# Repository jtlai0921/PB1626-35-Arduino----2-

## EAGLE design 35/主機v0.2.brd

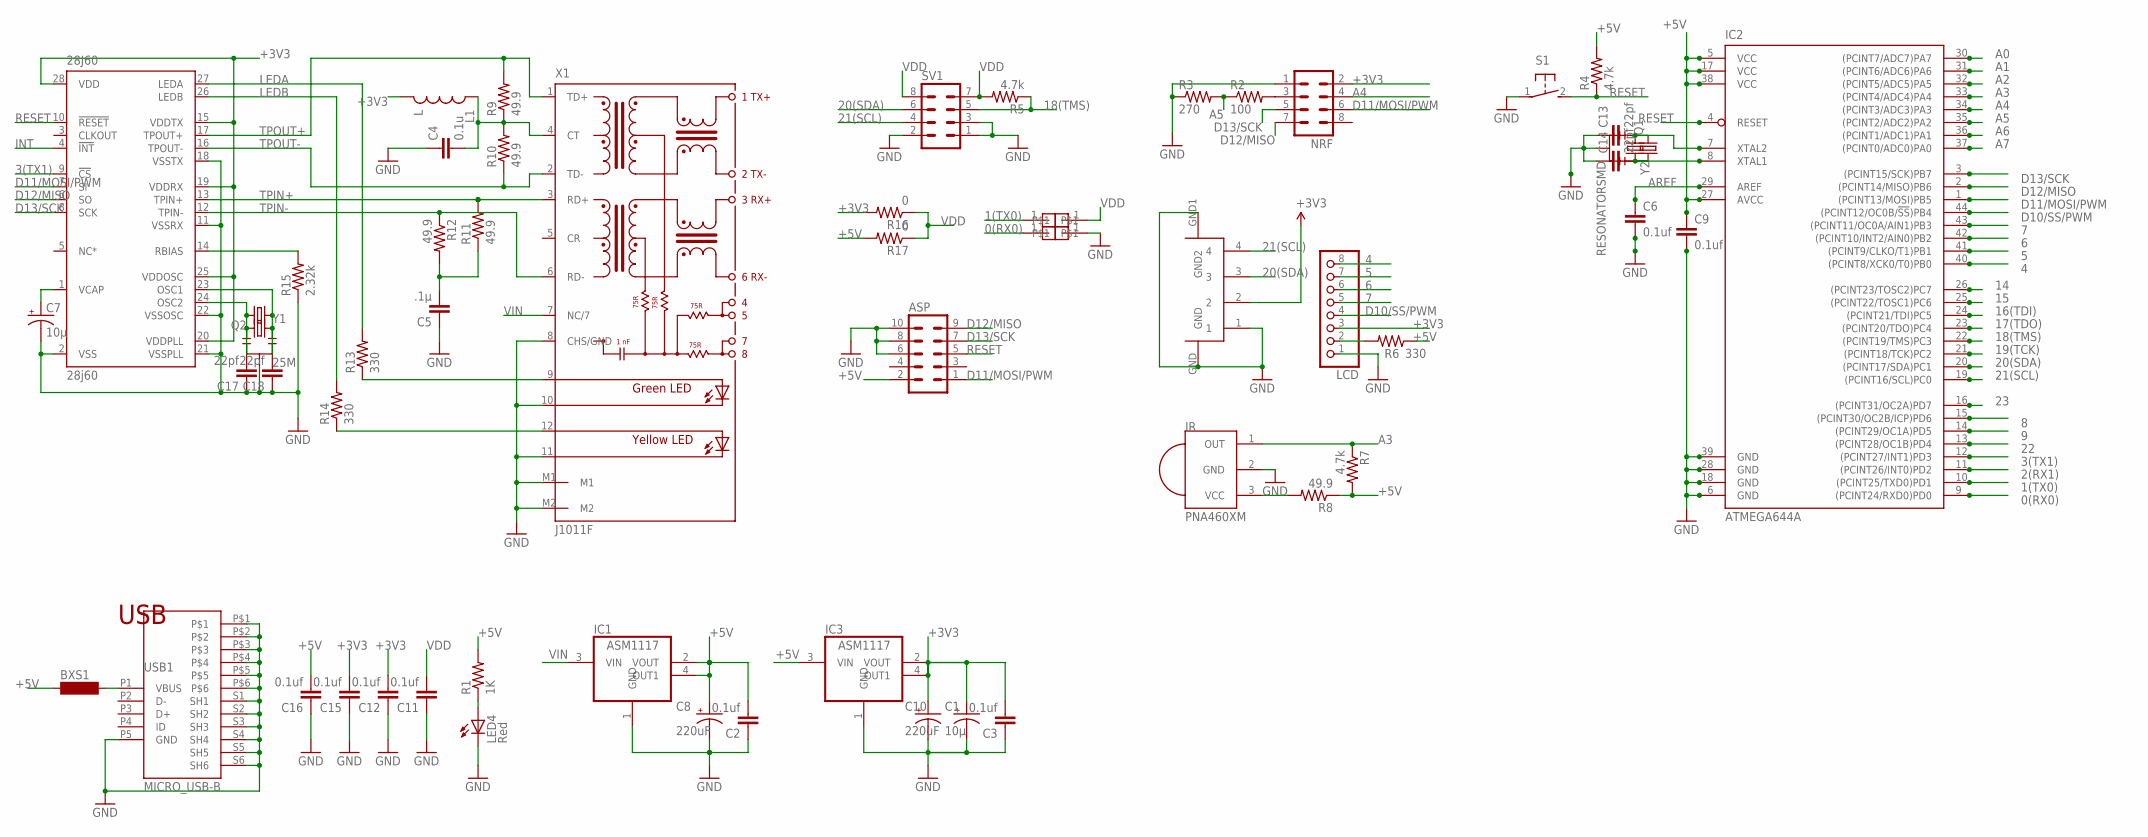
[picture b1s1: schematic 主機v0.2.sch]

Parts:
28J60: 28j60; SSOP28DB
ASP: MA05-2
BXS1: SM-1206
C1, C7: 10μ; EIA3528
C2, C3, C6, C9, C11, C12, C15, C16: 0.1uf; 0603-CAP
C4: 0.1u; 0603-CAP
C5: .1μ; 0603-CAP
C8, C10: 220uF; 153CLV-0605
C13, C14, C17, C18: 22pf; 0603-CAP
IC1: ASM1117; SOT223
IC2: ATMEGA644A; TQFP44
IC3: ASM1117; SOT223; MPN REG1117
IR: PNA460XM
L1: L; 0603
LCD: PINHD-1X8; 1X08
LED4: Red; 0805-LED
NRF: MA04-2
Q1, Q2: CRYSTALHC49S; HC49/S
R1: 1K; 0603-RES
R2: 100; 0603-RES
R3: 270; 0603-RES
R4, R5, R7: 4.7k; 0603-RES
R6, R13, R14: 330; 0603-RES
R8, R9, R10, R11, R12: 49.9; 0603-RES
R15: 2.32k; 0603-RES
R16, R17: 0; 0603-RES
S1: 31-XX; B3F-31XX
SV1: MA04-2
U$2: S4B-XH-SM4-TB; XH-SM4-TB
U$4, U$5, U$6, U$7: PIN1
USB1: MICRO_USB-B; USB_MICRO_B
X1: J1011F; HRJ
Y1: 25M; RESONATOR-SMD
Y2: RESONATORSMD; RESONATOR-SMD

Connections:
0(RX0): IC2.9 ((PCINT24/RXD0)PD0), U$7.1
1(TX0): IC2.10 ((PCINT25/TXD0)PD1), U$6.1
2(RX1): IC2.11 ((PCINT26/INT0)PD2)
3(TX1): 28J60.9 (!CS), IC2.12 ((PCINT27/INT1)PD3)
4: IC2.40 ((PCINT8/XCK0/T0)PB0), LCD.8
5: IC2.41 ((PCINT9/CLKO/T1)PB1), LCD.7
6: IC2.42 ((PCINT10/INT2/AIN0)PB2), LCD.6
7: IC2.43 ((PCINT11/OC0A/AIN1)PB3), LCD.5
8: IC2.15 ((PCINT30/OC2B/ICP)PD6)
9: IC2.14 ((PCINT29/OC1A)PD5)
14: IC2.26 ((PCINT23/TOSC2)PC7)
15: IC2.25 ((PCINT22/TOSC1)PC6)
16(TDI): IC2.24 ((PCINT21/TDI)PC5)
17(TDO): IC2.23 ((PCINT20/TDO)PC4)
18(TMS): IC2.22 ((PCINT19/TMS)PC3), R5.1, SV1.5
19(TCK): IC2.21 ((PCINT18/TCK)PC2)
20(SDA): IC2.20 ((PCINT17/SDA)PC1), SV1.6, U$2.3
21(SCL): IC2.19 ((PCINT16/SCL)PC0), SV1.4, U$2.4
22: IC2.13 ((PCINT28/OC1B)PD4)
23: IC2.16 ((PCINT31/OC2A)PD7)
+3V3: 28J60.15 (VDDTX), 28J60.19 (VDDRX), 28J60.20 (VDDPLL), 28J60.25 (VDDOSC), 28J60.28 (VDD), C1.A (+), C3.2, C10.+, C12.2, C15.2, IC3.2 (VOUT), IC3.4 (OUT1), L1.2, LCD.3, NRF.2, R16.2, U$2.2
+5V: ASP.2, BXS1.1, C2.2, C8.+, C9.1, C16.2, IC1.2 (VOUT), IC1.4 (OUT1), IC2.5 (VCC), IC2.17 (VCC), IC2.27 (AVCC), IC2.38 (VCC), IC3.3 (VIN), R1.2, R4.2, R6.1, R7.2, R8.1, R17.2
A0: IC2.30 ((PCINT7/ADC7)PA7)
A1: IC2.31 ((PCINT6/ADC6)PA6)
A2: IC2.32 ((PCINT5/ADC5)PA5)
A3: IC2.33 ((PCINT4/ADC4)PA4), IR.1 (OUT), R7.1
A4: IC2.34 ((PCINT3/ADC3)PA3), NRF.4
A5: IC2.35 ((PCINT2/ADC2)PA2), R2.1, R3.2
A6: IC2.36 ((PCINT1/ADC1)PA1)
A7: IC2.37 ((PCINT0/ADC0)PA0)
AREF: C6.1, IC2.29 (AREF)
D10/SS/PWM: IC2.44 ((PCINT12/OC0B/!SS!)PB4), LCD.4
D11/MOSI/PWM: 28J60.7 (SI), ASP.1, IC2.1 ((PCINT13/MOSI)PB5), NRF.6
D12/MISO: 28J60.6 (SO), ASP.9, IC2.2 ((PCINT14/MISO)PB6), NRF.7
D13/SCK: 28J60.8 (SCK), ASP.7, IC2.3 ((PCINT15/SCK)PB7), NRF.5
GND: 28J60.2 (VSS), 28J60.11 (VSSRX), 28J60.18 (VSSTX), 28J60.21 (VSSPLL), 28J60.22 (VSSOSC), ASP.6, ASP.8, ASP.10, C1.C (-), C2.1, C3.1, C4.1, C5.1, C6.2, C7.C (-), C8.-, C9.2, C10.-, C11.1, C12.1, C13.1, C14.1, C15.1, C16.1, C17.1, C18.1, IC1.1 (GND), IC2.6 (GND), IC2.18 (GND), IC2.28 (GND), IC2.39 (GND), IC3.1 (GND), IR.2 (GND), LCD.1, LED4.C, NRF.1, R3.1, R15.1, S1.1, SV1.1, SV1.2, SV1.3, U$2.1, U$2.GND, U$2.GND1 (GND2), U$4.1, USB1.P5 (GND), USB1.P$1, USB1.P$2, USB1.P$3, USB1.P$4, USB1.P$5, USB1.P$6, USB1.S1 (SH1), USB1.S2 (SH2), USB1.S3 (SH3), USB1.S4 (SH4), USB1.S5 (SH5), USB1.S6 (SH6), X1.8 (CHS/GND), X1.10 (C-R), X1.11 (C-L), X1.M1, X1.M2, Y1.2, Y2.2
INT: 28J60.4 (!INT)
LEDA: 28J60.27 (LEDA), R13.2
LEDB: 28J60.26 (LEDB), R14.2
unnamed: C13.2, IC2.7 (XTAL2), Q1.2, Y2.1
unnamed: IR.3 (VCC), R8.2
unnamed: LED4.A, R1.1
unnamed: NRF.3, R2.2
unnamed: C5.2, R11.1, R12.2
unnamed: 28J60.1 (VCAP), C7.A (+)
unnamed: 28J60.14 (RBIAS), R15.2
unnamed: C14.2, IC2.8 (XTAL1), Q1.1, Y2.3
unnamed: C4.2, L1.1, R9.1, R10.2, X1.4 (CT)
unnamed: 28J60.24 (OSC2), C17.2, Q2.2, Y1.1
unnamed: 28J60.23 (OSC1), C18.2, Q2.1, Y1.3
unnamed: R13.1, X1.9 (A-R)
unnamed: R14.1, X1.12 (AL)
unnamed: LCD.2, R6.2
RESET: 28J60.10 (!RESET), ASP.5, IC2.4 (RESET), R4.1, S1.2 (S)
TPIN+: 28J60.13 (TPIN+), R11.2, X1.3 (RD+)
TPIN-: 28J60.12 (TPIN-), R12.1, X1.6 (RD-)
TPOUT+: 28J60.17 (TPOUT+), R9.2, X1.1 (TD+)
TPOUT-: 28J60.16 (TPOUT-), R10.1, X1.2 (TD-)
VDD: C11.2, R5.2, R16.1, R17.1, SV1.7, SV1.8, U$5.1
VIN: IC1.3 (VIN), X1.7 (NC/7)
VUSB: BXS1.2, USB1.P1 (VBUS)

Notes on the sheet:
USB

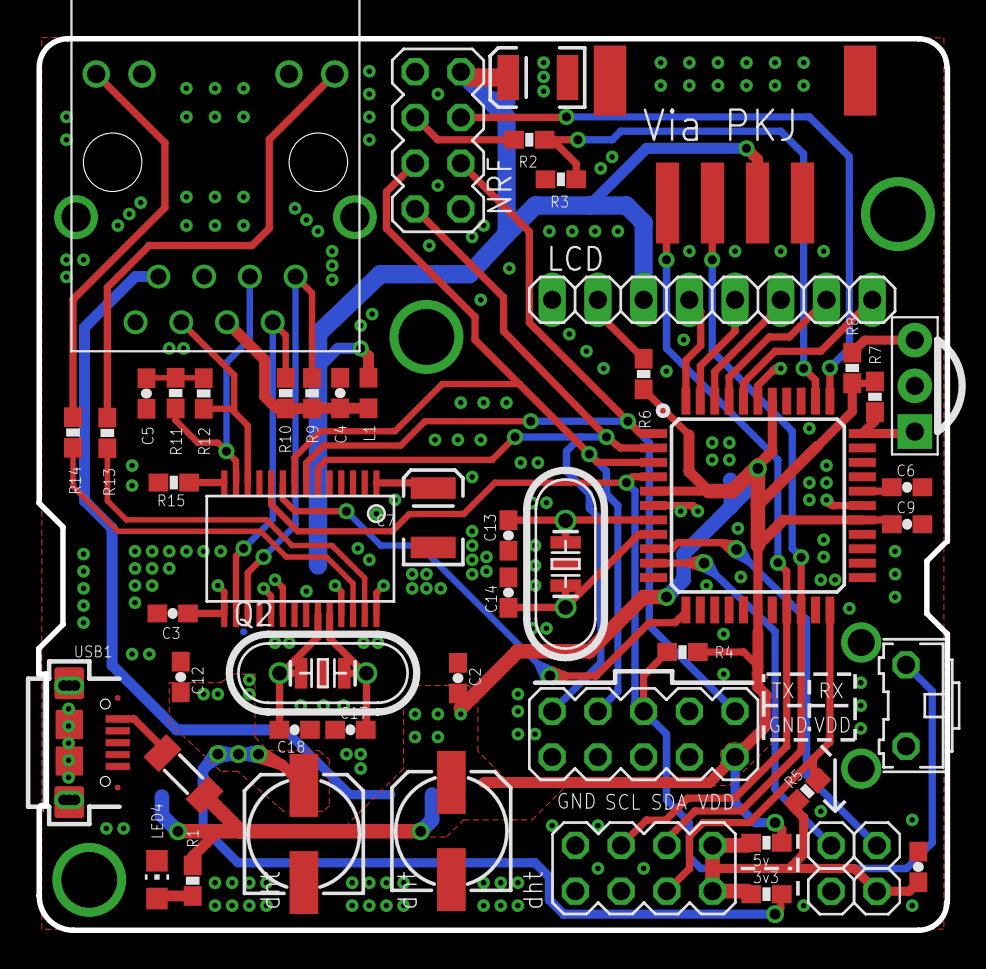
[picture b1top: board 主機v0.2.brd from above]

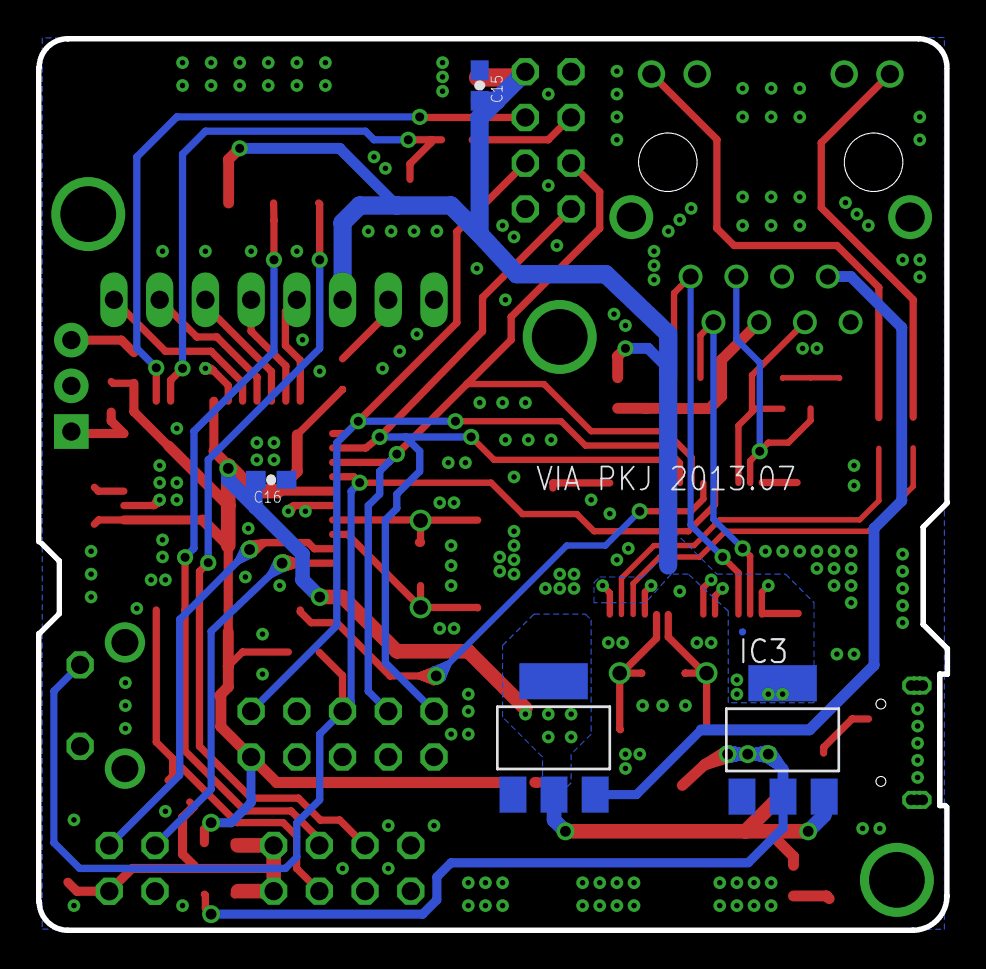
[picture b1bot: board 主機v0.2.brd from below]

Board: 2 copper layers, 50.5 x 49.5 mm, 59 parts (4 on the bottom side), 45 nets.

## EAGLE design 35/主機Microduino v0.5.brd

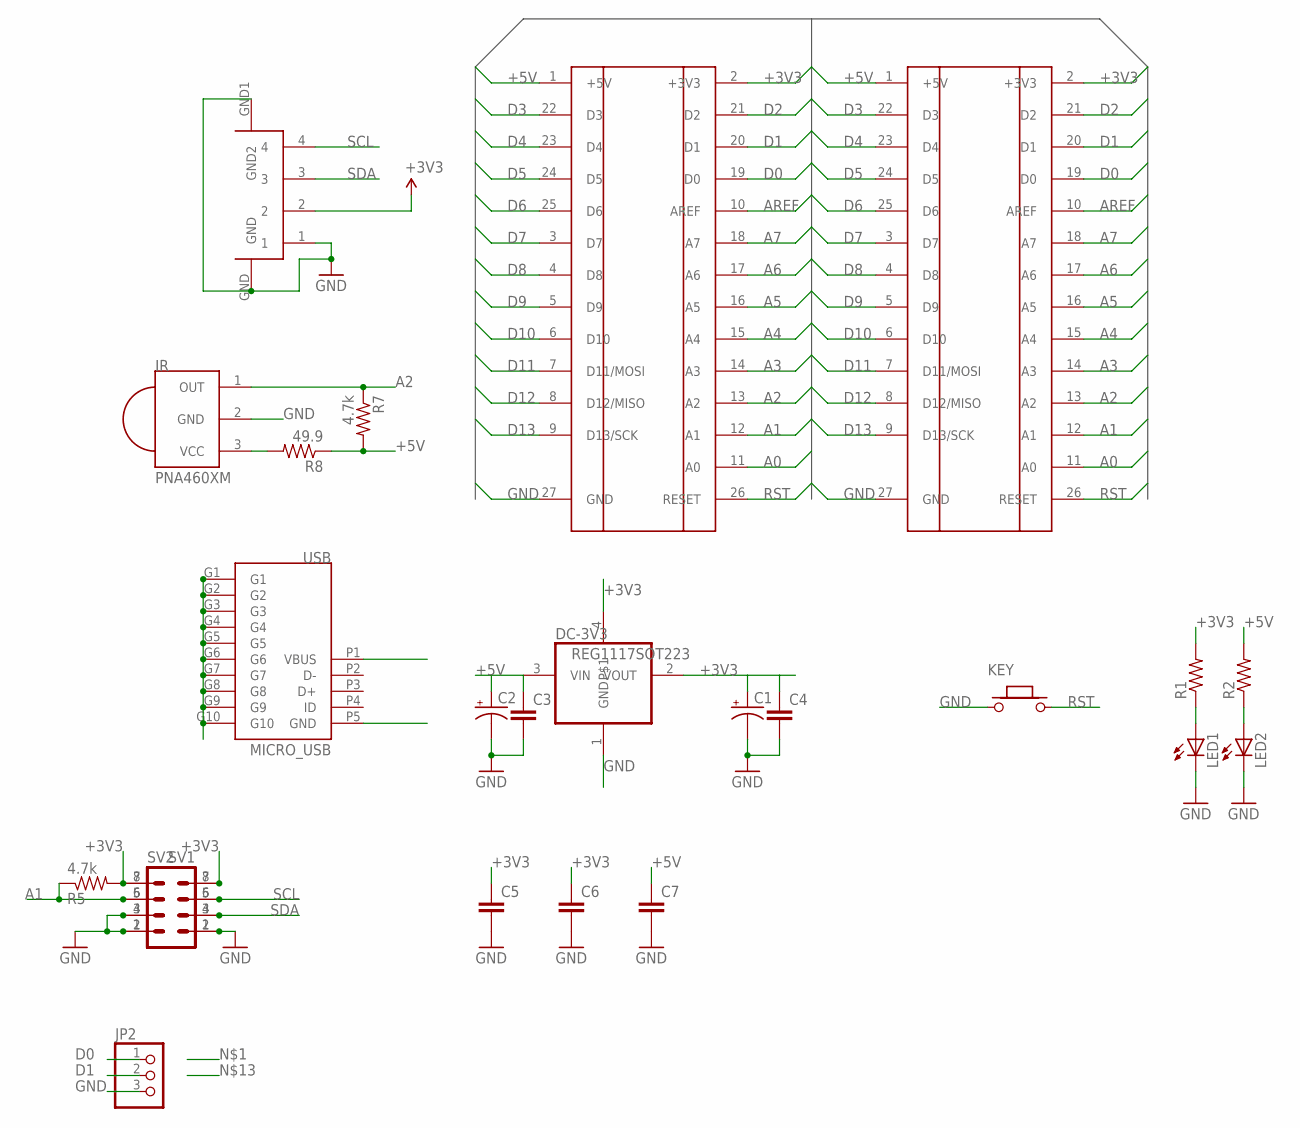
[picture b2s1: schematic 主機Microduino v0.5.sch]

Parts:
C1, C2: CAP_POL3528; EIA3528
C3, C4, C5, C6, C7: CAP0603-CAP; 0603-CAP
DC-3V3: REG1117SOT223; SOT223
IR: PNA460XM
JP2: PINHD-1X3; 1X03
KEY: KEY-TES-018; KEY-TS-018
LED1, LED2: LED0805; 0805-LED
R1, R2: RESISTOR0603-RES; 0603-RES
R5, R7: 4.7k; 0603-RES
R8: 49.9; 0603-RES
SV1, SV2: MA04-2
U$1, U$2: PING-MICRDUINO/1009; PIN-MICRODUINO-1009
U$3: S4B-XH-SM4-TB; XH-SM4-TB
USB: MICRO_USB; MICRO_USB_LJ

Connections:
+3V3: C1.A (+), C4.1, C5.1, C6.1, DC-3V3.2 (VOUT), DC-3V3.4, R1.2, R5.2, SV1.7, SV1.8, SV2.7, SV2.8, U$1.2 (+3V3), U$2.2 (+3V3), U$3.2
+5V: C2.A (+), C3.1, C7.1, DC-3V3.3 (VIN), R2.2, R7.2, R8.1, U$1.1 (+5V), U$2.1 (+5V), USB.P1 (VBUS)
A0: U$1.11 (A0), U$2.11 (A0)
A1: R5.1, SV1.5, SV2.6, U$1.12 (A1), U$2.12 (A1)
A2: IR.1 (OUT), R7.1, U$1.13 (A2), U$2.13 (A2)
A3: U$1.14 (A3), U$2.14 (A3)
A4: U$1.15 (A4), U$2.15 (A4)
A5: U$1.16 (A5), U$2.16 (A5)
A6: U$1.17 (A6), U$2.17 (A6)
A7: U$1.18 (A7), U$2.18 (A7)
AREF: U$1.10 (AREF), U$2.10 (AREF)
D0: JP2.1, U$1.19 (D0), U$2.19 (D0)
D1: JP2.2, U$1.20 (D1), U$2.20 (D1)
D2: U$1.21 (D2), U$2.21 (D2)
D3: U$1.22 (D3), U$2.22 (D3)
D4: U$1.23 (D4), U$2.23 (D4)
D5: U$1.24 (D5), U$2.24 (D5)
D6: U$1.25 (D6), U$2.25 (D6)
D7: U$1.3 (D7), U$2.3 (D7)
D8: U$1.4 (D8), U$2.4 (D8)
D9: U$1.5 (D9), U$2.5 (D9)
D10: U$1.6 (D10), U$2.6 (D10)
D11: U$1.7 (D11/MOSI), U$2.7 (D11/MOSI)
D12: U$1.8 (D12/MISO), U$2.8 (D12/MISO)
D13: U$1.9 (D13/SCK), U$2.9 (D13/SCK)
GND: C1.C (-), C2.C (-), C3.2, C4.2, C5.2, C6.2, C7.2, DC-3V3.1 (GND), IR.2 (GND), JP2.3, KEY.2 (1), LED1.C, LED2.C, SV1.1, SV1.2, SV1.3, SV2.1, SV2.2, SV2.4, U$1.27 (GND), U$2.27 (GND), U$3.1, U$3.GND, U$3.GND1 (GND2), USB.G1, USB.G2, USB.G3, USB.G4, USB.G5, USB.G6, USB.G7, USB.G8, USB.G9, USB.G10, USB.P5 (GND)
unnamed: IR.3 (VCC), R8.2
unnamed: LED1.A, R1.1
unnamed: LED2.A, R2.1
RST: KEY.1 (2), U$1.26 (RESET), U$2.26 (RESET)
SCL: SV1.6, SV2.5, U$3.4
SDA: SV1.4, SV2.3, U$3.3

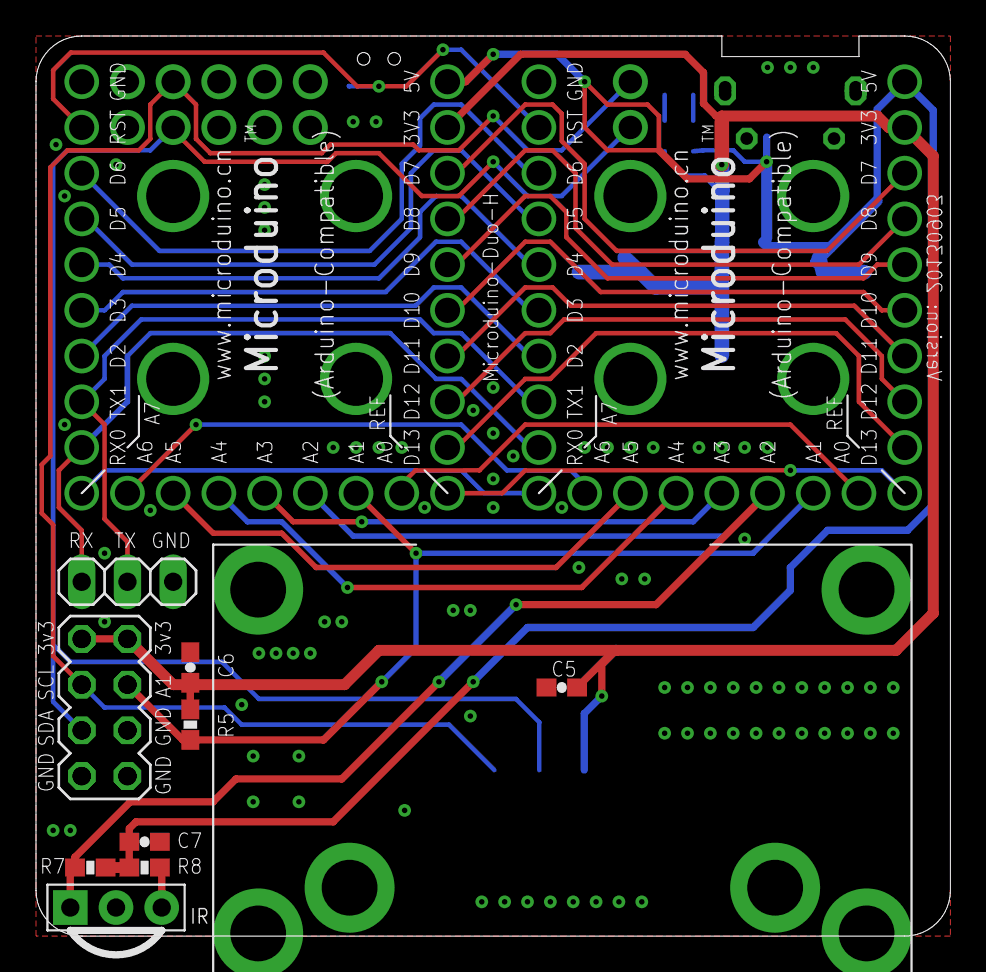
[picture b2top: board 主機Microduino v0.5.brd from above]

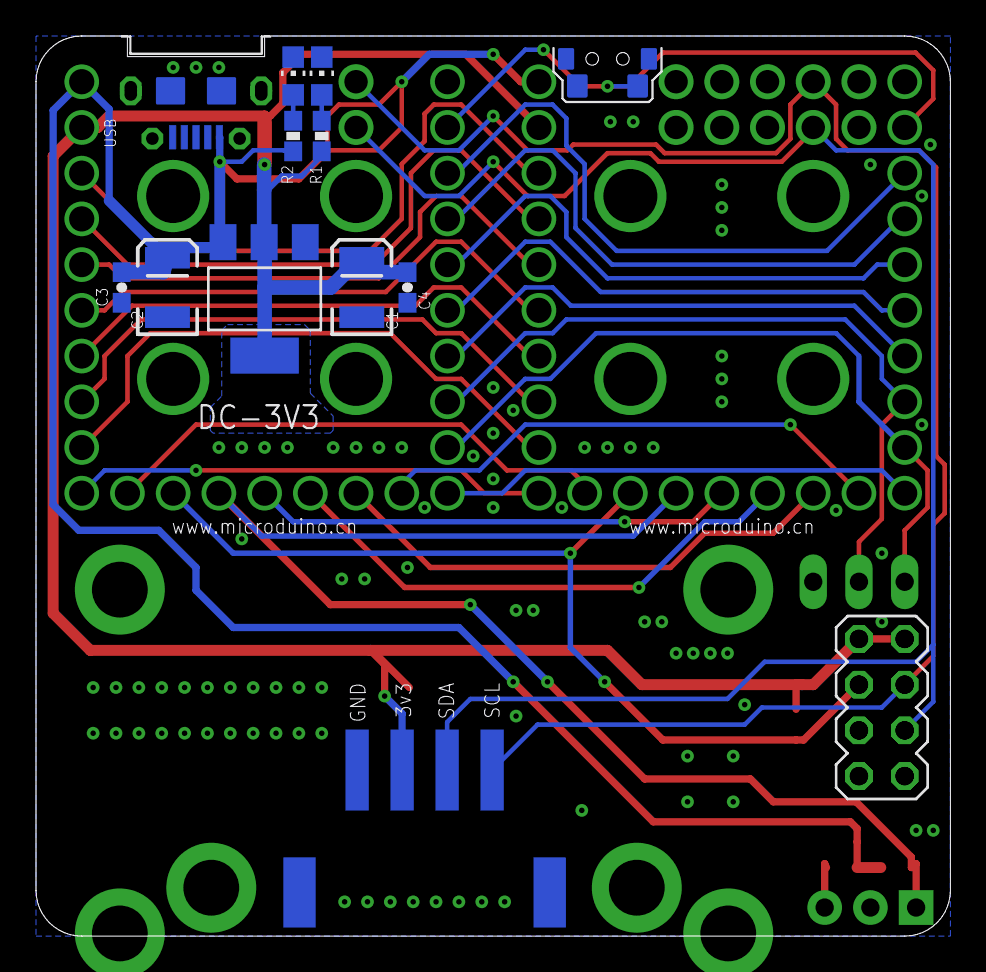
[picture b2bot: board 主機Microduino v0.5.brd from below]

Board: 2 copper layers, 50.8 x 50.0 mm, 24 parts (15 on the bottom side), 32 nets.
